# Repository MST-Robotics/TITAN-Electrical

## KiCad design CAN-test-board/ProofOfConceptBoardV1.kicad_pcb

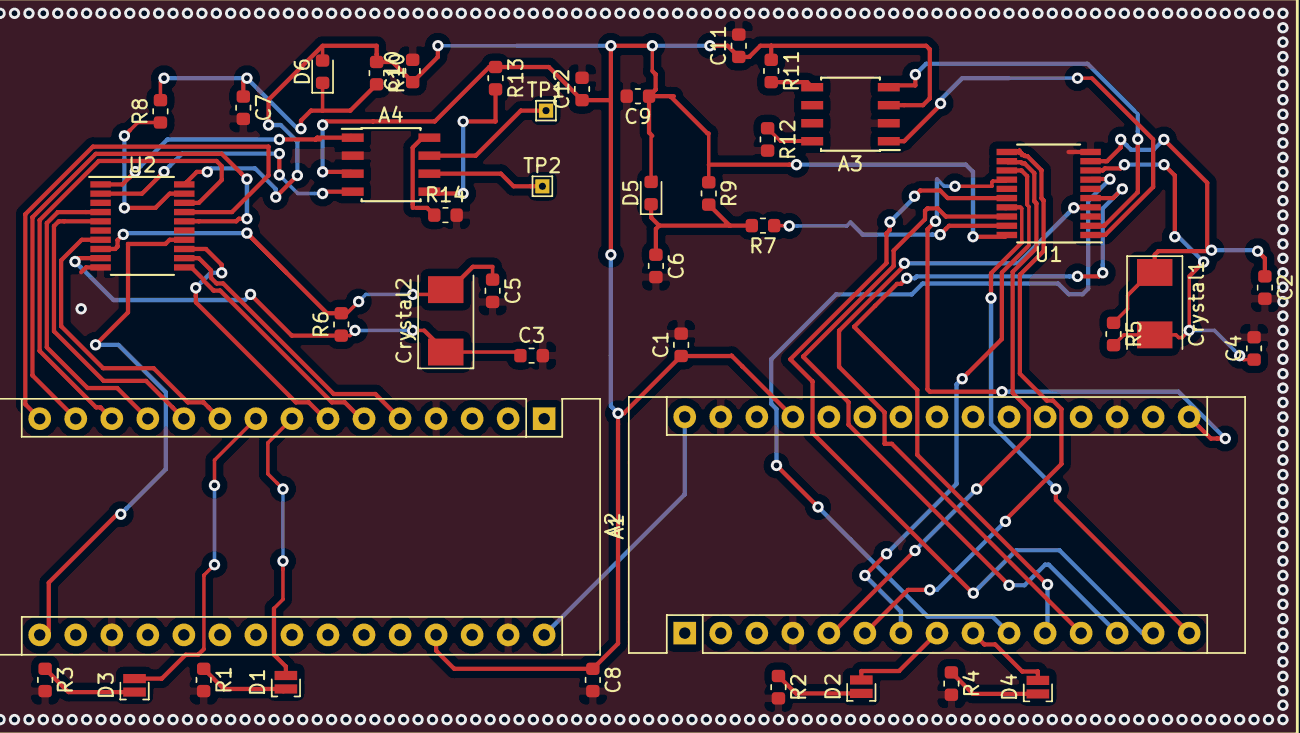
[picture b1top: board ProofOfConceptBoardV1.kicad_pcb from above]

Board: 2 copper layers, 42 parts (0 on the bottom side), 49 nets.

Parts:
A1, A2: Arduino_Nano_v3.x; Arduino_Nano
A3, A4: ATA6560; SOIC-8_3.9x4.9mm_P1.27mm
C1, C8, C9, C10, C11, C12: 100nF; C_0603_1608Metric
C2, C3, C4, C5: 15pF; C_0603_1608Metric
C6, C7: 1uF; C_0603_1608Metric
Crystal1: 20MHz; Crystal_SMD_0603-2Pin_6.0x3.5mm
Crystal2: 20 MHz; Crystal_SMD_0603-2Pin_6.0x3.5mm
D1, D2, D3, D4: LED; LED_Cree-XQ
D5, D6: DIODE; D_0603_1608Metric
R1, R2, R3, R4: 220; R_0603_1608Metric
R5, R6: 1M; R_0603_1608Metric
R7, R8, R11, R12, R13, R14: 10k; R_0603_1608Metric
R9, R10: 100k; R_0603_1608Metric
TP1, TP2: TestPoint; TestPoint_THTPad_1.0x1.0mm_Drill0.5mm
U1, U2: MCP2515-EST; TSSOP-20_4.4x6.5mm_P0.65mm

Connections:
+5V: A1.27, A2.27, A3.3, A4.3, C1.1, C8.1, C9.1, C10.1, C11.1, C12.1, D5.2, D6.2, R9.1, R10.1, R11.1, R13.1, U1.20, U2.20
CANRX: A3.4, U1.2
CANRX_2: A4.4, U2.2
CANTX: A3.1, U1.1
CANTX_2: A4.1, U2.1
GNDREF: A1.4, A1.18, A1.29, A2.4, A2.18, A2.29, A3.2, A4.2, C1.2, C2.2, C3.2, C4.2, C5.2, C6.2, C7.2, C8.2, C9.2, C10.2, C11.2, C12.2, R1.2, R2.2, R3.2, R4.2, R12.2, R14.2, U1.10, U2.10
INT0: A2.5, U1.12
INT0_2: A1.5, U2.12
INT1: A2.6, U1.11
INT1_2: A1.6, U2.11
INTMCP: A2.7, U1.13
INTMCP_2: A1.7, U2.13
MISO: A2.15, U1.17
MISO_2: A1.15, U2.17
MOSI: A2.14, U1.16
MOSI_2: A1.14, U2.16
unnamed: A1.8, D1.2
unnamed: A1.9, D3.2
unnamed: A2.8, D2.2
unnamed: A2.9, D4.2
unnamed: A3.5, R11.2
unnamed: A3.8, R12.1
unnamed: A4.5, R13.2
unnamed: A4.6, TP2.1
unnamed: A4.7, TP1.1
unnamed: A4.8, R14.1
unnamed: C6.1, D5.1, R7.2, R9.2
unnamed: C7.1, D6.1, R8.2, R10.2
unnamed: D1.1, R1.1
unnamed: D2.1, R2.1
unnamed: D3.1, R3.1
unnamed: D4.1, R4.1
unnamed: R7.1, U1.19
unnamed: R8.1, U2.19
OSC1: C2.1, Crystal1.1, R5.1, U1.9
OSC1_2: C3.1, Crystal2.1, R6.1, U2.9
OSC2: C4.1, Crystal1.2, R5.2, U1.8
OSC2_2: C5.1, Crystal2.2, R6.2, U2.8
SCK: A2.16, U1.14
SCK_2: A1.16, U2.14
SS: A2.13, U1.18
SS_2: A1.13, U2.18
TBUF0: A2.10, U1.7
TBUF0_2: A1.10, U2.7
TBUF1: A2.11, U1.5
TBUF1_2: A1.11, U2.5
TBUF2: A2.12, U1.4
TBUF2_2: A1.12, U2.4
VCC: A1.30, A2.30

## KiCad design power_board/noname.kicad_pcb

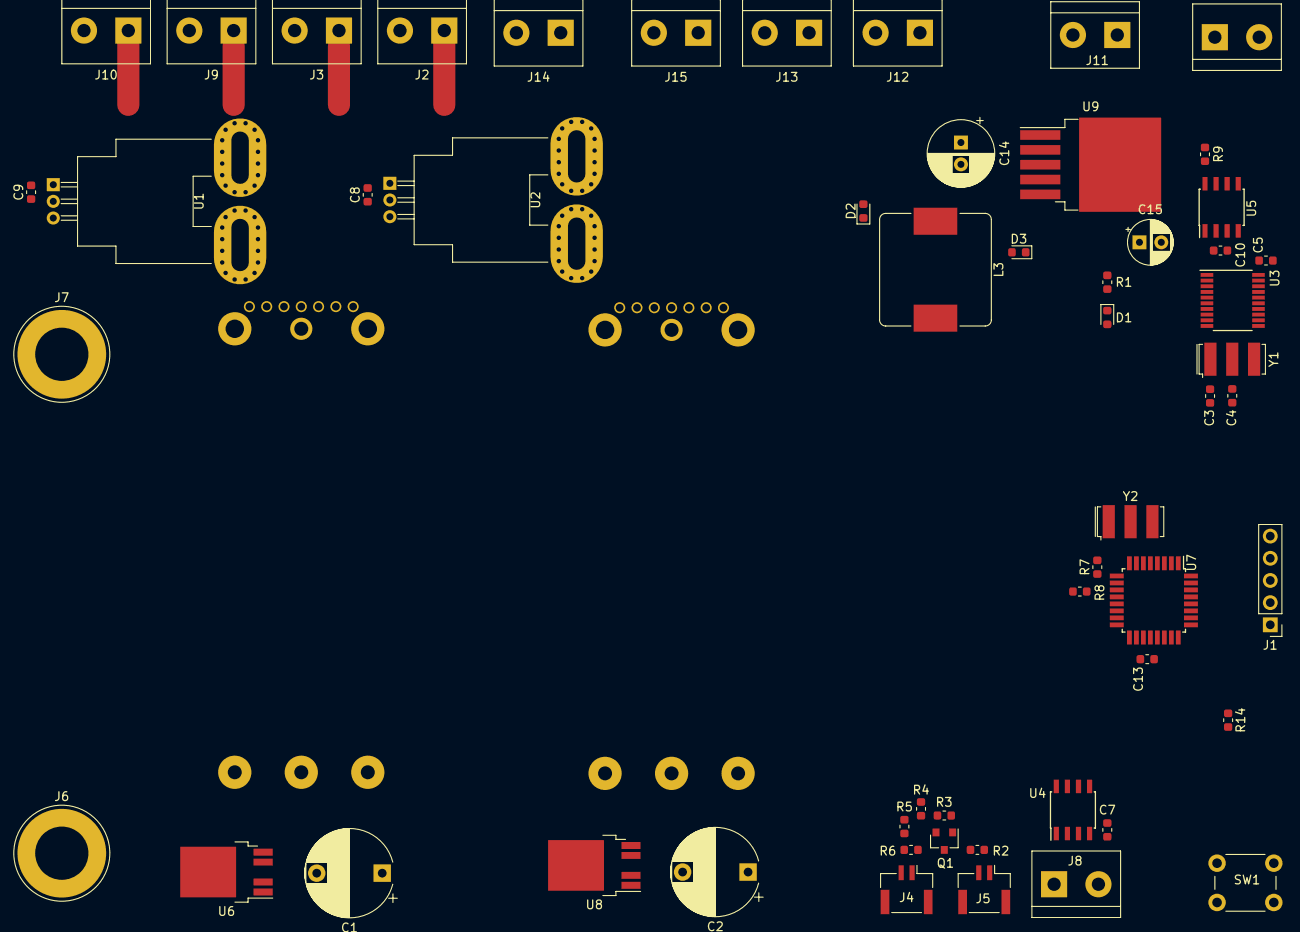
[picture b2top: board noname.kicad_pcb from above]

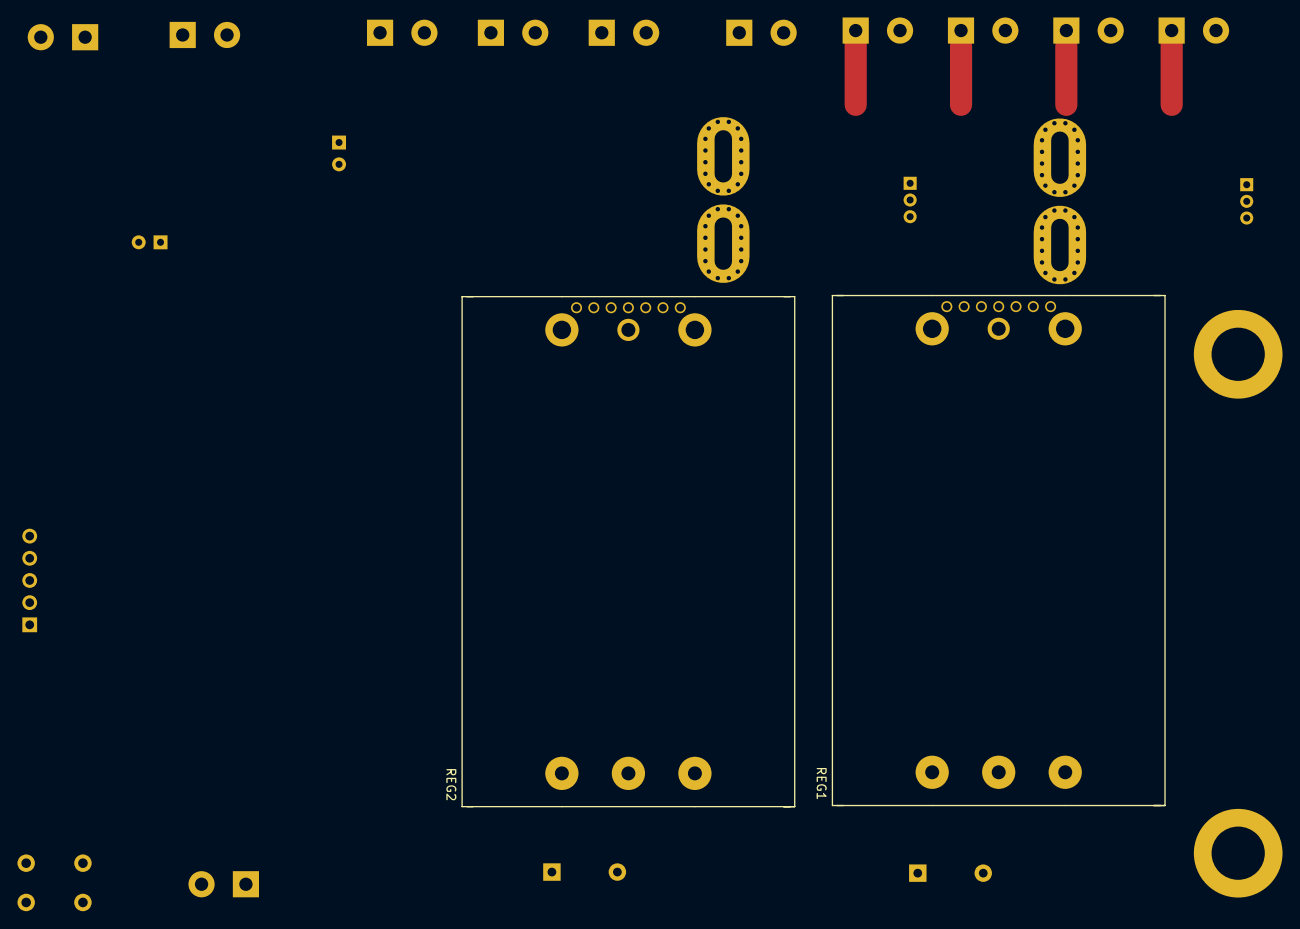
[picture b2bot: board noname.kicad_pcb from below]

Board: 2 copper layers, 57 parts (2 on the bottom side), 43 nets.

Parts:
C1, C2: 300uF; CP_Radial_D10.0mm_P7.50mm
C3, C4: 22pF; C_0603_1608Metric
C5, C7, C8, C9, C10, C13: 0.1uF; C_0603_1608Metric
C14: 680uF; CP_Radial_D7.5mm_P2.50mm
C15: 220uF; CP_Radial_D5.0mm_P2.50mm
D1: LED; LED_0603_1608Metric
D2: 1N5824; D_0603_1608Metric
D3: --; D_0603_1608Metric
J1: PROG; PinHeader_1x05_P2.54mm_Vertical
J2: M1; TerminalBlock_bornier-2_P5.08mm
J3: M2; TerminalBlock_bornier-2_P5.08mm
J4, J5: Conn_01x02_Female; JST_GH_BM02B-GHS-TBT_1x02-1MP_P1.25mm_Vertical
J6, J7: Conn_01x01_Male; Banana_Jack_1Pin
J8, J16: Screw_Terminal_01x02; TerminalBlock_bornier-2_P5.08mm
J9: M3; TerminalBlock_bornier-2_P5.08mm
J10: M4; TerminalBlock_bornier-2_P5.08mm
J11: MainBoard; TerminalBlock_bornier-2_P5.08mm
J12: M5; TerminalBlock_bornier-2_P5.08mm
J13: M6; TerminalBlock_bornier-2_P5.08mm
J14: M7; TerminalBlock_bornier-2_P5.08mm
J15: FAN; TerminalBlock_bornier-2_P5.08mm
L3: 33uH; L_Bourns_SRP1245A
Q1: 2N3906; SOT-23
R1: 330; R_0603_1608Metric
R2: 1k; R_0603_1608Metric
R3, R4, R6, R7, R8, R14: 10k; R_0603_1608Metric
R5: 1.1k; R_0603_1608Metric
R9: 4.7k; R_0603_1608Metric
REG1, REG2: StepDownConverter; Q54SG
SW1: SW_Push; SW_PUSH_6mm
U1, U2: ACS758xCB-050B-PFF; Allegro_CB_PFF
U3: MCP2515-EST; TSSOP-20_4.4x6.5mm_P0.65mm
U4: MAX31855KASA; SOIC-8_3.9x4.9mm_P1.27mm
U5: MCP2551-I-SN; SOIC-8_3.9x4.9mm_P1.27mm
U6, U8: BTS6163D; TO-252-4
U7: ATmega328P-AU; TQFP-32_7x7mm_P0.8mm
U9: LM2596S-5; TO-263-5_TabPin3
Y1, Y2: 16Mhz; Resonator_SMD-3Pin_7.2x3.0mm

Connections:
12VA_IN: REG2.4, U2.4
12VA_SENSE: U2.3, U7.24
12V_IN: REG1.4, U1.4
12V_SENSE: U1.3, U7.23
+5V: C5.1, C7.1, C8.1, C9.1, C10.1, C13.1, D1.2, D3.1, J1.1, J11.1, R7.2, R8.1, R14.1, U1.2, U2.2, U3.20, U4.4, U5.3, U7.4, U7.6, U7.18
+5VA: Q1.2, R3.2, R4.1, R5.2
+12V: J2.1, J3.1, J9.1, J10.1, U1.5
+12VA: C14.1, J12.1, J13.1, J14.1, J15.1, U2.5, U9.1
+48V: J6.1, R4.2, U6.3, U8.3
CANH: J16.1, U5.7
CANL: J16.2, U5.6
CAN_CS: R7.1, U3.18, U7.9
CAN_INT: U3.13, U7.32
CAN_RX: U3.2, U5.4
CAN_TX: U3.1, U5.1
GNDREF: C1.2, C2.2, C3.1, C4.2, C5.2, C7.2, C8.2, C9.2, C10.2, C13.2, C14.2, C15.2, D2.2, J1.5, J2.2, J3.2, J4.1, J5.1, J7.1, J9.2, J10.2, J11.2, J12.2, J13.2, J14.2, J15.2, R1.2, R5.1, R6.1, R9.1, REG1.2, REG1.3, REG1.6, REG2.2, REG2.3, REG2.6, SW1.2, U1.1, U2.1, U3.10, U4.1, U5.2, U7.3, U7.5, U7.21, U9.3, U9.5, Y2.2
MISO: U3.17, U4.7, U7.16
MOSI: U3.16, U7.15
unnamed: C1.1, REG1.1, U6.1, U6.5
unnamed: C2.1, REG2.1, U8.1, U8.5
unnamed: C3.2, U3.8, U3.15, Y1.1
unnamed: C4.1, U3.9, Y1.2
unnamed: C15.1, D3.2, L3.2, U9.4
unnamed: D1.1, R1.1
unnamed: D2.1, L3.1, U9.2
unnamed: J4.2, J5.2, R2.1
unnamed: J8.1, U4.2
unnamed: J8.2, U4.3
unnamed: Q1.1, R2.2, R3.1
unnamed: R9.2, U5.8
unnamed: U7.7, Y2.3
unnamed: U7.8, Y2.1
RESET: J1.2, R14.2, SW1.1, U3.19, U7.29
RX: J1.4, U7.30
RX1BF: U3.11, U7.25
RX_INT: U3.12, U7.1
SCK: U3.14, U4.5, U7.17
SHUTOFF: Q1.3, R6.2, U6.2, U8.2
TC_CS: R8.2, U4.6, U7.10
TX: J1.3, U7.31
TX0RTS: U3.4, U7.26
TX1RTS: U3.5, U7.27
TX2RTS: U3.7, U7.28
